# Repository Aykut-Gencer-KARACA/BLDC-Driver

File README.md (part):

<div align="center">

<br/>

<br/><br/>

**Sıfırdan tasarlanmış bir fırçasız DC (BLDC) motor sürücüsü.**<br/>
Hall sensörü olmadan, boştaki fazın back-EMF sıfır geçişini okuyarak rotor konumunu tahmin eder.

<br/>

<sub>PCB'nin Blender'da hazırlanmış 3D render'ı · tam çözünürlüklü video için görsele tıklayın</sub>

</div>

<!--
  ────────────────────────────────────────────────────────────────────────────
  OYNATILABİLİR VİDEO (isteğe bağlı)
  GitHub, repodaki .mp4 dosyalarını README içinde oynatıcı olarak GÖSTERMEZ.
  Oynatıcı istiyorsanız:
    1) GitHub'da README.md'yi web editöründe açın (kalem simgesi).
    2) assets/pcb-render.mp4 dosyasını editöre sürükleyip bırakın.
    3) Oluşan https://github.com/user-attachments/assets/... satırını
       aşağıdaki "VIDEO_LINKI_BURAYA" satırının yerine koyun (tek başına, kendi satırında).
    4) Bu yorum bloğunu silebilirsiniz.
  ────────────────────────────────────────────────────────────────────────────
-->

<!-- VIDEO_LINKI_BURAYA -->

## İçindekiler

- [Genel bakış](#-genel-bakış)
- [Öne çıkanlar](#-öne-çıkanlar)
- [Sistem mimarisi](#-sistem-mimarisi)
- [Six-step komütasyon](#-six-step-komütasyon)
- [Donanım](#-donanım)
- [Tasarım hesapları](#-tasarım-hesapları)
- [Pin haritası](#-pin-haritası)
- [PCB](#-pcb)
- [Malzeme listesi](#-malzeme-listesi)
- [Depo yapısı](#-depo-yapısı)

## ◆ Genel bakış

Bu proje, bir **A2212 1000 KV** fırçasız motoru **3S LiPo** batarya ile sürmek için tasarlanmış bir ESC'dir (Electronic Speed Controller). Kart; güç girişi koruması, iki ayrı regülatör, 3 fazlı MOSFET köprüsü, faz başına bağımsız akım ölçümü, back-EMF algılama ve bir **STM32F405** mikrodenetleyiciyi tek bir PCB üzerinde topluyor.

Tasarımdaki her değer bir hesaba dayanıyor: MOSFET seçiminden bootstrap kondansatörüne, dead-time'dan ferrit bead bastırma oranına kadar kararların gerekçesi [Tasarım hesapları](#-tasarım-hesapları) bölümünde.

| Özellik | Değer |
|---|---|
| **Kontrol yöntemi** | Sensörsüz six-step (trapezoidal), back-EMF sıfır geçişi |
| **Giriş gerilimi** | 3S LiPo · 11.1 V nominal · 12.6 V maksimum |
| **Faz akımı** | 10 A sürekli · 12 A tepe (tasarım hedefi) |
| **Anahtarlama** | 30 kHz, center-aligned PWM |
| **Dead-time** | 2 katman: TIM1 DTG ≈ 1 µs + DRV8300 sabit ≈ 215 ns (tipik) |
| **Akım ölçümü** | 3 × low-side şönt (10 mΩ) + 3 × INA180A1 (20 V/V), eşzamanlı örnekleme |
| **Hız ayarı** | Panel montaj 10 kΩ potansiyometre |
| **Programlama** | SWD (ST-Link V2) |

## ◆ Öne çıkanlar

<table>
<tr>
<td width="50%" valign="top">

**Katmanlı giriş koruması**<br/>
TVS diyot (SMBJ13A, 14.4 V'ta iletime başlar), 20 A SMD sigorta ve P-kanal ters polarite MOSFET (SP40P04AGHNK). Hot-plug ve anahtarlama kaynaklı gerilim darbelerine karşı koruma.

</td>
<td width="50%" valign="top">

**Faz başına eşzamanlı akım ölçümü**<br/>
Üç şönt ve üç back-EMF kanalı üç ayrı ADC'ye dağıtıldı (ADC1/2/3). TIM1 CH4 tetiklediği anda üç ADC *injected simultaneous* modda aynı sıradaki kanalları aynı anda örnekliyor; fazlar arası zaman kayması yok, DMA gerekmiyor.

</td>
</tr>
<tr>
<td valign="top">

**Isıl hesabı yapılmış MOSFET seçimi**<br/>
DON100N04 (40 V, < 3.5 mΩ, **Q<sub>g</sub> ≈ 40 nC** @ 10 V). 10.5 A'de MOSFET başına ≈ 0.39 W (25 °C); sıcakken (4.46 mΩ) ≈ 0.49 W ve 40 °C ortamda T<sub>J</sub> ≈ 65 °C. Bu kartta tek MOSFET'in ısıl sınırı ≈ 22 A.

</td>
<td valign="top">

**Temiz analog besleme**<br/>
VDDA hattı ferrit bead + 100 nF + 1 µF ile buck ripple'ından ayrıldı. 500 kHz'de tahmini **30–60 kat bastırma** (geçen kısım ≈ %1.6–3). ADC referansı ve CSA beslemesi aynı hattan: ölçüm oransal (ratiometric).

</td>
</tr>
<tr>
<td valign="top">

**Hesaplanmış bootstrap**<br/>
C<sub>BOOT,min</sub> ≈ 47 nF (TI'ın 1 V dalgalanma kuralı), seçilen 100 nF ile **~2× pay** ve ≈ 0.47 V dalgalanma. Üst kol kesintisiz açık kalamayacağı için %100 duty kullanılmıyor.

</td>
<td valign="top">

**Sanal nötr ile back-EMF algılama**<br/>
Faz başına 20 kΩ / 4.99 kΩ bölücü 12.6 V'u ≈ 2.52 V'a indiriyor; 3 × 20 kΩ + 1.65 kΩ'luk sanal nötr aynı ölçekte (sapma ≈ %0.7). Boştaki fazın nötrü kestiği an sıfır geçişi.

</td>
</tr>
</table>

## ◆ Sistem mimarisi

Güç yolu soldan sağa akıyor: batarya, sırasıyla sigorta (F1) ve ters polarite MOSFET'inden (Q7) geçip `V_BUS` barasına ulaşıyor; TVS diyodu (D1) Q7'nin hemen arkasında, bara ile GND arasındadır. Bu baradan üç kol ayrılıyor:

- **TPS54202 buck** → 3.3 V (MCU, CSA'lar, potansiyometre) · 500 kHz senkron
- **BA00BC0WFP LDO** → 8 V GVDD (DRV8300 gate sürme beslemesi) · ≈ 5 mA tipik, en fazla ≈ 11 mA yük
- **3 faz köprü** → motor fazları A / B / C

STM32, TIM1'in 6 tamamlayıcı PWM çıkışıyla DRV8300'ü sürüyor; DRV8300 de bootstrap üzerinden üst kol N-kanal MOSFET'lerin gate'lerini bara geriliminin üstüne taşıyor.

## ◆ Six-step komütasyon

Her elektriksel periyot altı adıma bölünüyor. Her adımda **iki faz aktif** (biri üst koldan PWM'leniyor, diğeri alt koldan sürekli iletimde), **üçüncü faz boşta** kalıyor. Boştaki fazın back-EMF'i sanal nötr seviyesini kestiği anda (sıfır geçişi) rotorun konumu biliniyor ve bir sonraki adıma geçiş zamanlanıyor.

| Adım | 1 | 2 | 3 | 4 | 5 | 6 |
|:--|:-:|:-:|:-:|:-:|:-:|:-:|
| **Üst kol (PWM)** | A | A | B | B | C | C |
| **Alt kol (açık)** | B | C | C | A | A | B |
| **Boşta (BEMF ölçümü)** | C | B | A | C | B | A |

> [!NOTE]
> Motor dururken back-EMF olmadığı için sensörsüz kontrolde **açık döngü başlatma** (open-loop ramp) gerekiyor. Motor yeterli hıza ulaşıp BEMF okunabilir hale geldiğinde kapalı döngüye geçiliyor.

## ◆ Donanım

<details open>
<summary><b>Güç katı</b></summary>
<br/>

| Blok | Parça | Not |
|---|---|---|
| Yarım köprü MOSFET'leri | 6 × **DON100N04** (DFN-8) | 40 V · < 3.5 mΩ · Q<sub>g</sub> ≈ 40 nC · gövde diyodu yeterli, harici Schottky yok |
| Gate dirençleri | 6 × 15 Ω | TI referans tasarımı ve bağımsız hesapla doğrulandı |
| Gate pull-down | 6 × 10 kΩ | Self turn-on koruması |
| Faz kondansatörleri | Faz başına 100 µF + 1 µF + 100 nF | Bulk + decoupling |

</details>

<details>
<summary><b>Gate sürücü — DRV8300</b></summary>
<br/>

- DT pini boşta (ya da GND'de): dahili dead-time ≈ 215 ns (tipik, datasheet)
- Bootstrap: 100 nF, entegre bootstrap diyodu
- GVDD: 8 V LDO çıkışı
- nFAULT çıkışı yok → donanımsal aşırı akım kesmesi (BKIN) yok; akım, şönt + INA180 zinciriyle ölçülüyor

</details>

<details>
<summary><b>Akım ölçümü</b></summary>
<br/>

- 3 × **10 mΩ / 3 W** şönt (2512), alt kol altında (low-side)
- 3 × **INA180A1** (20 V/V) — 12 A'de 2.4 V çıkış
- Çıkışta 100 Ω + 22 nF RC filtre (f<sub>c</sub> ≈ 72 kHz)
- 12-bit ADC ile çözünürlük ≈ **4 mA / LSB**

</details>

<details>
<summary><b>Back-EMF algılama</b></summary>
<br/>

- Faz başına bölücü: 20 kΩ / 4.99 kΩ → 12.6 V faz geriliminde **≈ 2.52 V** ADC girişi
- Sanal nötr: 3 × 20 kΩ yıldız + 1.65 kΩ (R<sub>n</sub> = R<sub>alt</sub>/3) → faz bölücüleriyle aynı ölçek
- Tüm dirençler ±%1; ölçek sapması ≈ %0.7

</details>

<details>
<summary><b>Mikrodenetleyici — STM32F405RGT6</b></summary>
<br/>

- Cortex-M4F · 168 MHz · 1 MB Flash · 192 KB RAM · FPU
- Sıcaklık sınıfı: −40…85 °C (RGT6) · datasheet DS8626
- 8 MHz HSE kristal, 2 × 30 pF yük kondansatörü (C<sub>L</sub> = 20 pF)
- VCAP1/2: 2 × 2.2 µF X5R
- 4 × VDD'ye ayrı 100 nF + ortak 4.7 µF (C47), VBAT → 3.3 V + 100 nF
- NRST: 100 nF + tact switch · BOOT0: 10 kΩ ile GND
- SWD: 4 pinlik 2.54 mm header (3.3 V, SWDIO, SWCLK, GND)

</details>

<details>
<summary><b>Göstergeler (LED)</b></summary>
<br/>

| LED | Görev | Sürüş | Akım |
|---|---|---|---|
| LED1 | Güç göstergesi | 3.3 V → R38 (200 Ω) → LED1 → GND | ≈ 6.5 mA |
| LED2 | SWD aktivite göstergesi | 3.3 V → R39 (200 Ω) → LED2 → Q8 (MMBT5551, low-side) · baz SWCLK'ten R40 (10 kΩ) ile | ≈ 6.5 mA |

- LED2, debugger bağlıyken SWCLK üzerindeki trafikle yanıp söner; MCU pini harcamaz.
- Q8'in baz akımı ≈ 0.26 mA — SWCLK hattını anlamlı ölçüde yüklemez.

</details>

## ◆ Tasarım hesapları

<details>
<summary><b>Giriş koruması: sigorta, ters polarite MOSFET'i, TVS</b></summary>
<br/>

**Sigorta (F1).** 20 A, gecikmeli (time-lag), 32 V DC. Gecikmeli olması motorun kalkış anındaki kısa süreli yüksek akımda gereksiz atmayı önler; 20 A, 10 A'lik çalışma akımının iki katıdır.

**Ters polarite MOSFET'i (Q7, SP40P04AGHNK).** Kayıp karşılaştırması, R<sub>DS(on)</sub> = 4.7 mΩ (V<sub>GS</sub> = −10 V'ta en fazla; tipik 3.7 mΩ) ile:

$$\text{Q7 ile: } P = I^2 \times R_{DS(on)} = 10^2 \times 0.0047 \approx 0.47\text{ W}$$

$$\text{Schottky diyotla: } P = V_F \times I \approx 0.45\text{ V} \times 10\text{ A} \approx 4.5\text{ W}$$

Fark yaklaşık 10 kattır (tipik dirençle ≈ 12 kat). Q7'nin gate–source arasına normalde en fazla 12.6 V gelir; SP40P04AGHNK'nin V<sub>GS</sub> sınırı ±20 V, V<sub>DS</sub> sınırı −40 V'tur.

**TVS (D1, SMBJ13A).** Çalışma gerilimi (V<sub>RWM</sub>) 13 V'tur: 3S'in 12.6 V'luk dolu gerilimine kadar neredeyse hiç akım çekmez (en fazla 5 µA). 14.4–16.5 V arasında iletime başlar (V<sub>BR</sub>) ve en büyük darbe akımında (I<sub>PP</sub> = 27.9 A) gerilimi 21.5 V'ta kenetler (V<sub>C</sub>).

Bu değerler kartın en hassas parçalarına göre seçildi. Bataryadan doğrudan beslenen BA00BC0WFP'nin girişi en fazla 18 V, TPS54202'nin en fazla 30 V'tur; Q7'nin gate–source gerilimi de bara gerilimine eşit olduğu için sınırı ±20 V'tur. Küçük ve orta büyüklükteki darbelerde D1, gerilimi 15–17 V civarında tutar ve bu parçaların hepsi sınırın altında kalır. Yalnızca TVS'in tam nominal darbe akımına yaklaşan çok büyük bir darbede kenetleme gerilimi 18 V'un ve ±20 V'un üstüne çıkabilir. 40 V'luk köprü MOSFET'leri her durumda korunur. 13 V'luk TVS, normal çalışma gerilimiyle iletim eşiği arasında küçük bir pay bırakır; bu yüzden kart yalnızca 3S için uygundur, 4S batarya bağlanmamalıdır.

**Ters bağlantıda D1.** D1 tek yönlü bir TVS'tir ve şemada Q7'nin arkasında, bara tarafındadır. Ters bağlantıda Q7 kapalı kalır ve gövde diyodu ters kutuplanır; bara, D1 dahil, bataryadan ayrılır. Bu yüzden D1 iletime geçmez, F1 atmaz ve kart zarar görmez.

</details>

<details>
<summary><b>MOSFET seçimi</b></summary>
<br/>

Anahtarlama anında akım bir MOSFET'ten diğerine devredilirken yoldaki parazit endüktans aşım üretir:

$$\Delta V \approx L_{\text{parazit}} \times \frac{di}{dt} \qquad\text{(örnek: } 10\text{ nH} \times 0.5\text{ A/ns} = 5\text{ V)}$$

Bu yüzden pratikte bara geriliminin en az 2 katı alınır:

$$V_{DS} \geq 2 \times V_{\text{bara,max}} = 2 \times 12.6\text{ V} = 25.2\text{ V} \quad\Rightarrow\quad 40\text{ V sınıfı}$$

$$I_D \geq 3 \times I_{\text{çalışma}} = 3 \times 10\text{ A} = 30\text{ A} \quad\Rightarrow\quad \text{DON100N04: 100 A}$$

İletim kaybı, 25 °C'de $R_{DS(on)} \leq 3.5\text{ m}\Omega$ ile:

$$P = I^2 \times R_{DS(on)} = 10.5^2 \times 0.0035 \approx 0.39\text{ W}$$

Asıl karar ısıl hesapla verilir. Datasheet'teki 100 A (T<sub>C</sub> = 25 °C) ve 59 A (T<sub>C</sub> = 125 °C) değerleri, sonsuz soğutucu varsayımıyla (R<sub>θCA</sub> = 0) yapılmış ısı hesabıdır: $P_{max} = 25/1.6 \approx 15.6\text{ W}$, $I_D = \sqrt{15.6/0.00446} \approx 59\text{ A}$. Bu kartta soğutucu yoktur; ısı PCB bakırından havaya atılır. Sıcakken (150 °C) direnç ≈ 4.46 mΩ, R<sub>θJA</sub> = 50 °C/W ve T<sub>A</sub> = 40 °C ile:

$$P = 10.5^2 \times 0.00446 \approx 0.49\text{ W} \quad\Rightarrow\quad T_J = T_A + P \times R_{\theta JA} = 40 + 0.49 \times 50 \approx 65\text{ °C}$$

$$I_{max} = \sqrt{\frac{(150 - 40)/50}{0.00446}} = \sqrt{\frac{2.2\text{ W}}{0.00446\ \Omega}} \approx 22\text{ A}$$

Yani bu kartta tek bir MOSFET'in sürekli taşıyabileceği akım datasheet'teki 100 A değil, yaklaşık 22 A'dir. Datasheet'teki en kötü parça (25 °C'de 3.5 mΩ, tipikten ≈ 1.25 kat dirençli) için P ≈ 0.61 W ve T<sub>J</sub> ≈ 71 °C olur; sonuç değişmez. Six-step'te bir MOSFET bir elektriksel turun yalnızca bir kısmında akım taşıdığı için gerçek ortalama ısı bundan da düşüktür.

</details>

<details>
<summary><b>Bara kondansatörleri</b></summary>
<br/>

Üst MOSFET her açıldığında motor akımı (≈ 10 A) bir anda bu kola akmak ister; batarya kablo ve PCB izlerinin endüktansı yüzünden bu ani talebe yetişemez. Bu yüzden her kolun yanına faz başına 100 µF + 1 µF + 100 nF konur: 100 µF'lık elektrolitik yükün büyük kısmını depolar, 1 µF ve 100 nF'lık seramikler MHz mertebesindeki hızlı akım değişimlerini karşılar. Kondansatörlerin MOSFET'lerin dibinde olması hızlı akım döngüsünü kısaltır, aşımı azaltır. Motor sargısı bu döngünün içinde değildir; endüktansı büyük olduğu için anahtarlama süresince sabit bir akım kaynağı gibi davranır.

</details>

<details>
<summary><b>Gate sürme: neden sürücü, gate direnci, tepe ve ortalama akım</b></summary>
<br/>

STM32 MOSFET'leri doğrudan süremez:

1. **Gerilim yetmez:** pin en fazla 3.3 V verir; MOSFET'in R<sub>DS(on)</sub> değeri 4.5 V ve 10 V için verilmiştir.
2. **Akım yetmez:** 40 nC'luk gate'i bir GPIO'nun 25 mA'iyle doldurmak $t \approx Q_g / I = 40\text{ nC} / 25\text{ mA} \approx 1.6\ \mu\text{s}$ sürer; DRV8300'ün 0.75 A'iyle aynı süre ≈ 53 ns'dir.
3. **Üst MOSFET'in gate'i baranın üstüne çıkmalı:** source 12.6 V'a çıkınca gate ≈ 20 V civarında olmalıdır; bunu sürücü bootstrap devresiyle üretir.

15 Ω seri gate direnci gate'in dolma hızını yumuşatır (di/dt ve aşım düşer) ve sürücünün tepe akımını sınırlar; daha büyük direnç daha yumuşak ama daha yavaş (daha sıcak) anahtarlama demektir. 10 kΩ pull-down gate'i source seviyesinde tutar.

$$I_{\text{tepe}} = \frac{V_{GVDD}}{R_{toplam}} = \frac{8\text{ V}}{15\ \Omega} \approx 0.53\text{ A}$$

Sürücünün ve MOSFET'in iç dirençleri eklendiği için gerçek tepe akım bunun biraz altında kalır; DRV8300'ün 750 mA'lik (tipik) açma ve 1.5 A'lik kapama akımının altındadır.

$$I_{\text{ort}} \approx \frac{I_{\text{tepe}}}{2} = \frac{0.53}{2} \approx 0.27\text{ A} \qquad t_{\text{şarj}} \approx \frac{Q_g}{I_{\text{ort}}} = \frac{32\text{ nC}}{0.27\text{ A}} \approx 120\text{ ns}$$

120 ns, 30 kHz'lik PWM periyodunun (33 µs) binde dördü kadardır. Gate 8 V ile sürüldüğü için taşınan yük ≈ 32 nC'dur; hesaplarda 40 nC kullanmak güvenli taraftır.

</details>

<details>
<summary><b>Bootstrap kondansatörü</b></summary>
<br/>

Üst kol MOSFET'ini iletimde tutmak için gate'in source'un 8 V üstünde olması gerekir; source bara gerilimine (12.6 V) fırladığı için gate sabit 8 V ile sürülemez. Gate, SH ile birlikte yükselip alçalan bir kondansatörden (C<sub>boot</sub>) beslenir:

- **Şarj fazı:** alt MOSFET iletimdeyken SH ≈ 0 V; GVDD, DRV8300 içindeki bootstrap diyodu üzerinden kondansatörü doldurur. Diyot düşümü (en fazla 0.85 V) yüzünden kondansatörde 8 − 0.85 ≈ 7.15 V birikir.
- **Sürüş fazı:** üst MOSFET iletime geçer, SH 12.6 V'a çıkar; kondansatörün üst ucu 12.6 + 7.15 ≈ 19.8 V'ta kalır ve gate bu noktadan beslenir.

Kondansatörün boyutu (TI'ın yöntemiyle, V<sub>GVDD</sub> = 8 V, Q<sub>g</sub> = 40 nC, f<sub>sw</sub> = 30 kHz):

$$\Delta V_{BST} = V_{GVDD} - V_{BOOTD} - V_{BSTUV} = 8 - 0.85 - 4.5 = 2.65\text{ V}$$

$$Q_{tot} = Q_g + \frac{I_{LBS,TRAN}}{f_{sw}} = 40\text{ nC} + \frac{220\ \mu\text{A}}{30\text{ kHz}} \approx 47\text{ nC}$$

TI, kondansatör üzerindeki çevrim başına dalgalanmanın 1 V'u geçmemesini öneriyor:

$$C_{BOOT,min} = \frac{Q_{tot}}{1\text{ V}} \approx 47\text{ nF} \quad\Rightarrow\quad 100\text{ nF seçildi (yaklaşık 2 kat pay)}$$

100 nF ile dalgalanma $47\text{ nC} / 100\text{ nF} \approx 0.47\text{ V}$, yani 2.65 V'luk sınırın çok altında. GVDD tarafında kural $C_{GVDD} \geq 10 \times C_{BOOT} = 1\ \mu\text{F}$; datasheet GVDD pininde ayrıca en az 10 µF istiyor (C43 = 10 µF, C40 = 1 µF, C42 = 100 nF).

</details>

<details>
<summary><b>GVDD akım bütçesi ve LDO</b></summary>
<br/>

8 V'un gerekçesi: MOSFET tam açılmalı (8 V, datasheet'in R<sub>DS(on)</sub> verdiği 10 V'a yakındır), sürücünün GVDD kilidinden (4.35 V) uzak durulmalı ve batarya boşalırken gate sürüşü sabit kalmalı. Akım çok küçük (≈ 11 mA) olduğu için LDO'nun kaybı önemsizdir.

Six-step'te her an yalnızca PWM uygulanan koldaki iki MOSFET anahtarlanır:

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
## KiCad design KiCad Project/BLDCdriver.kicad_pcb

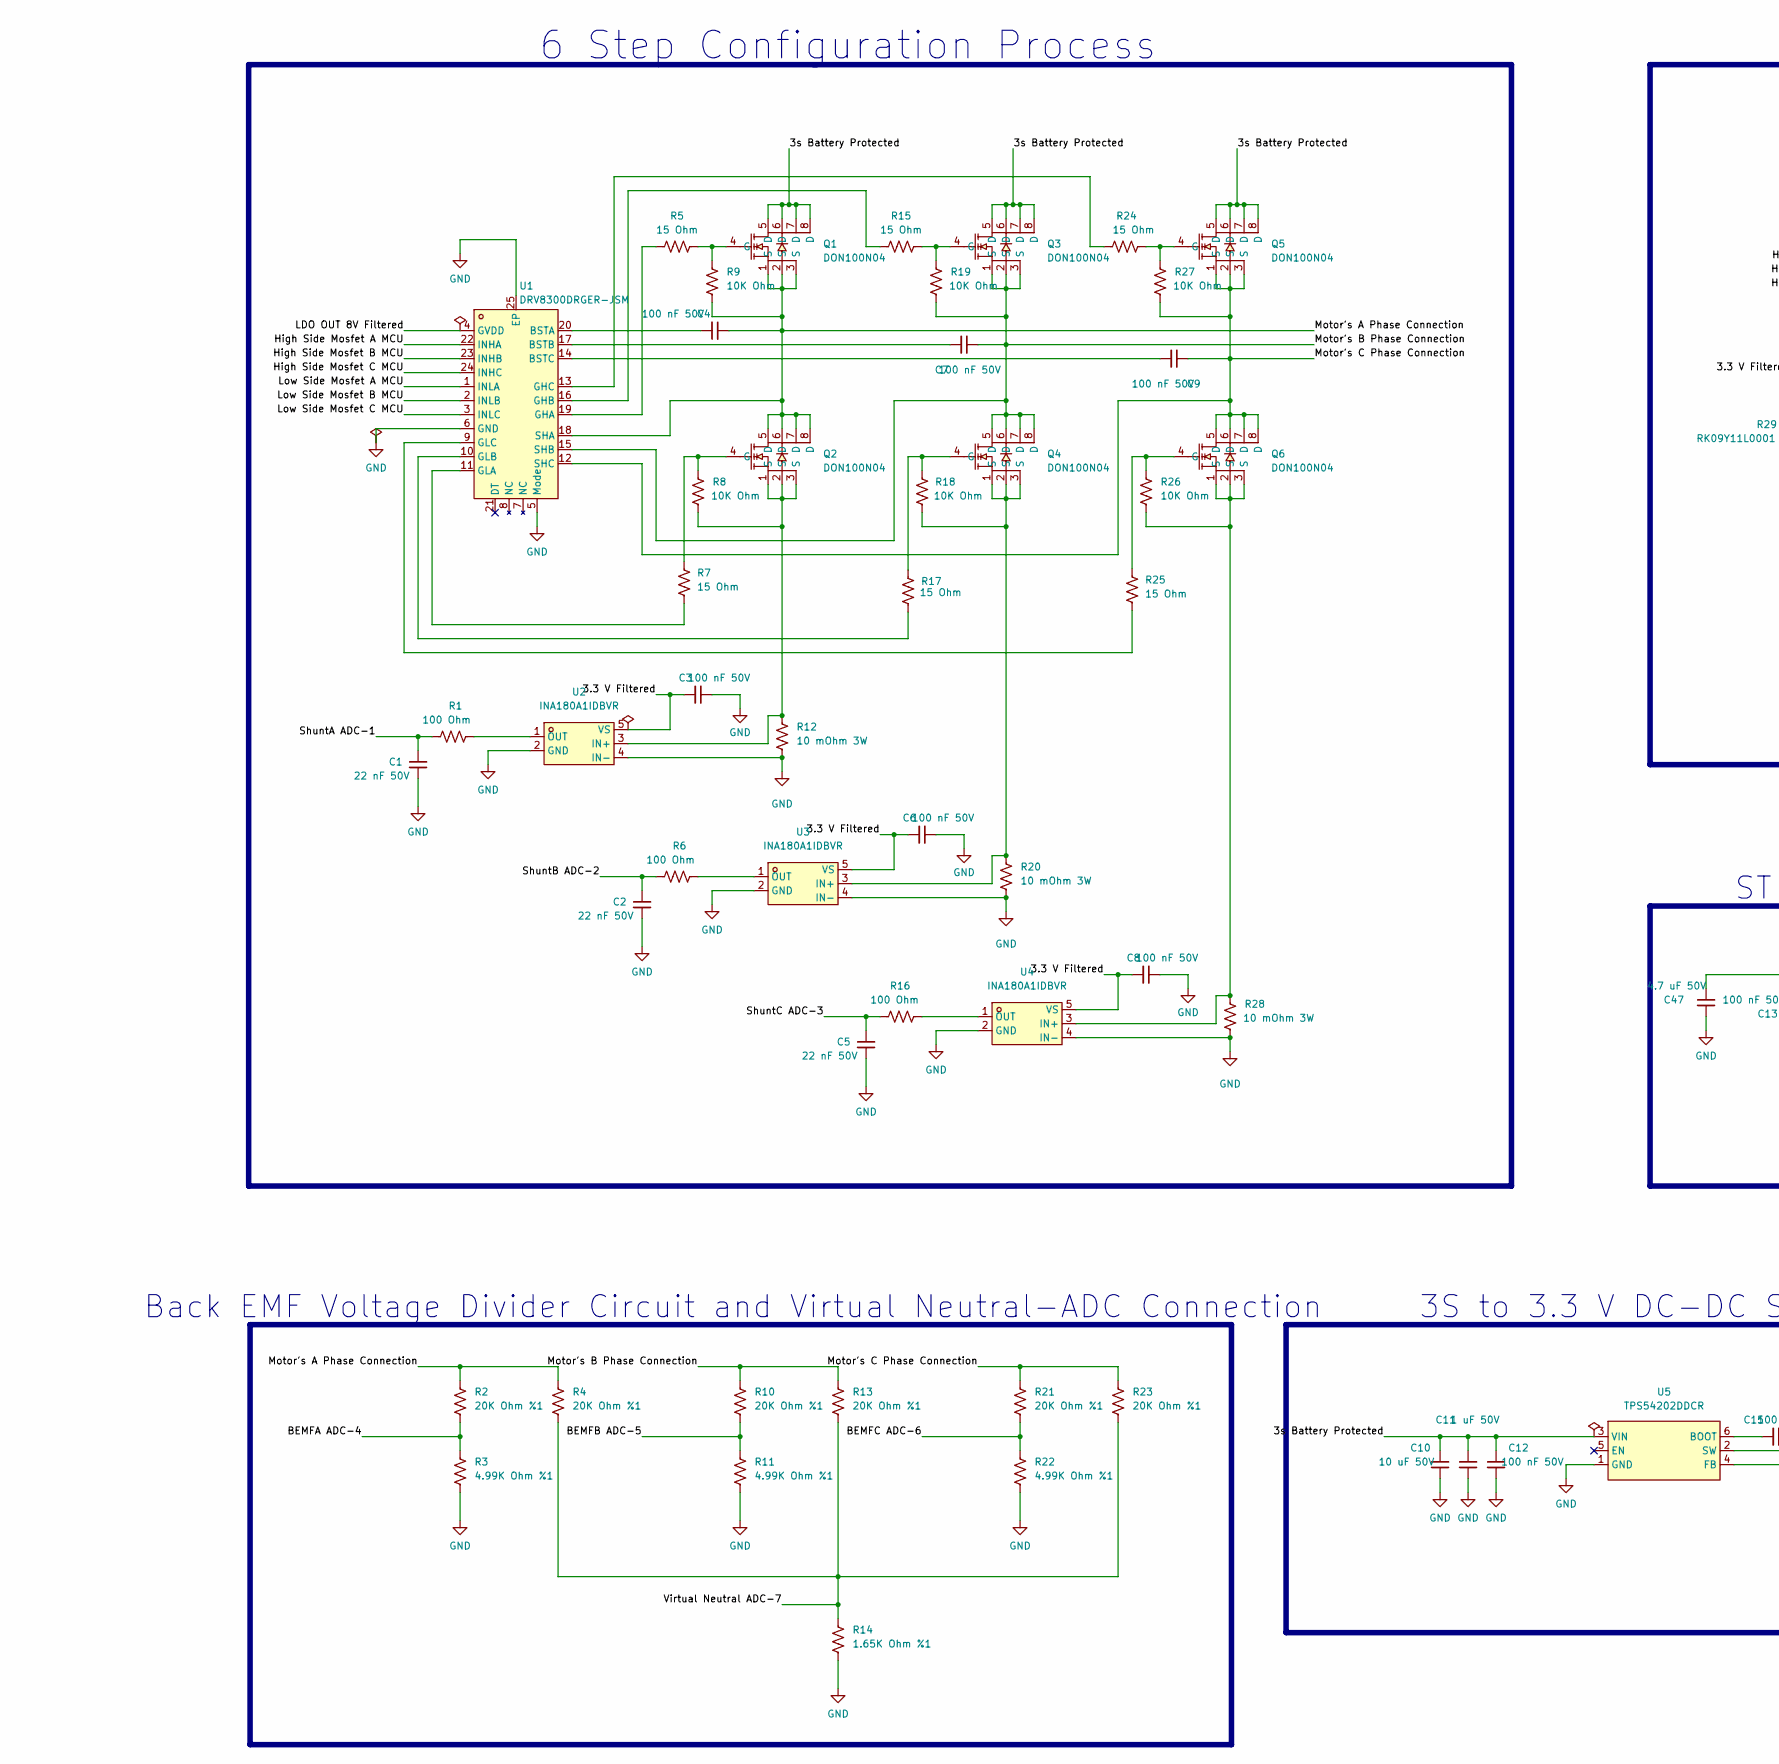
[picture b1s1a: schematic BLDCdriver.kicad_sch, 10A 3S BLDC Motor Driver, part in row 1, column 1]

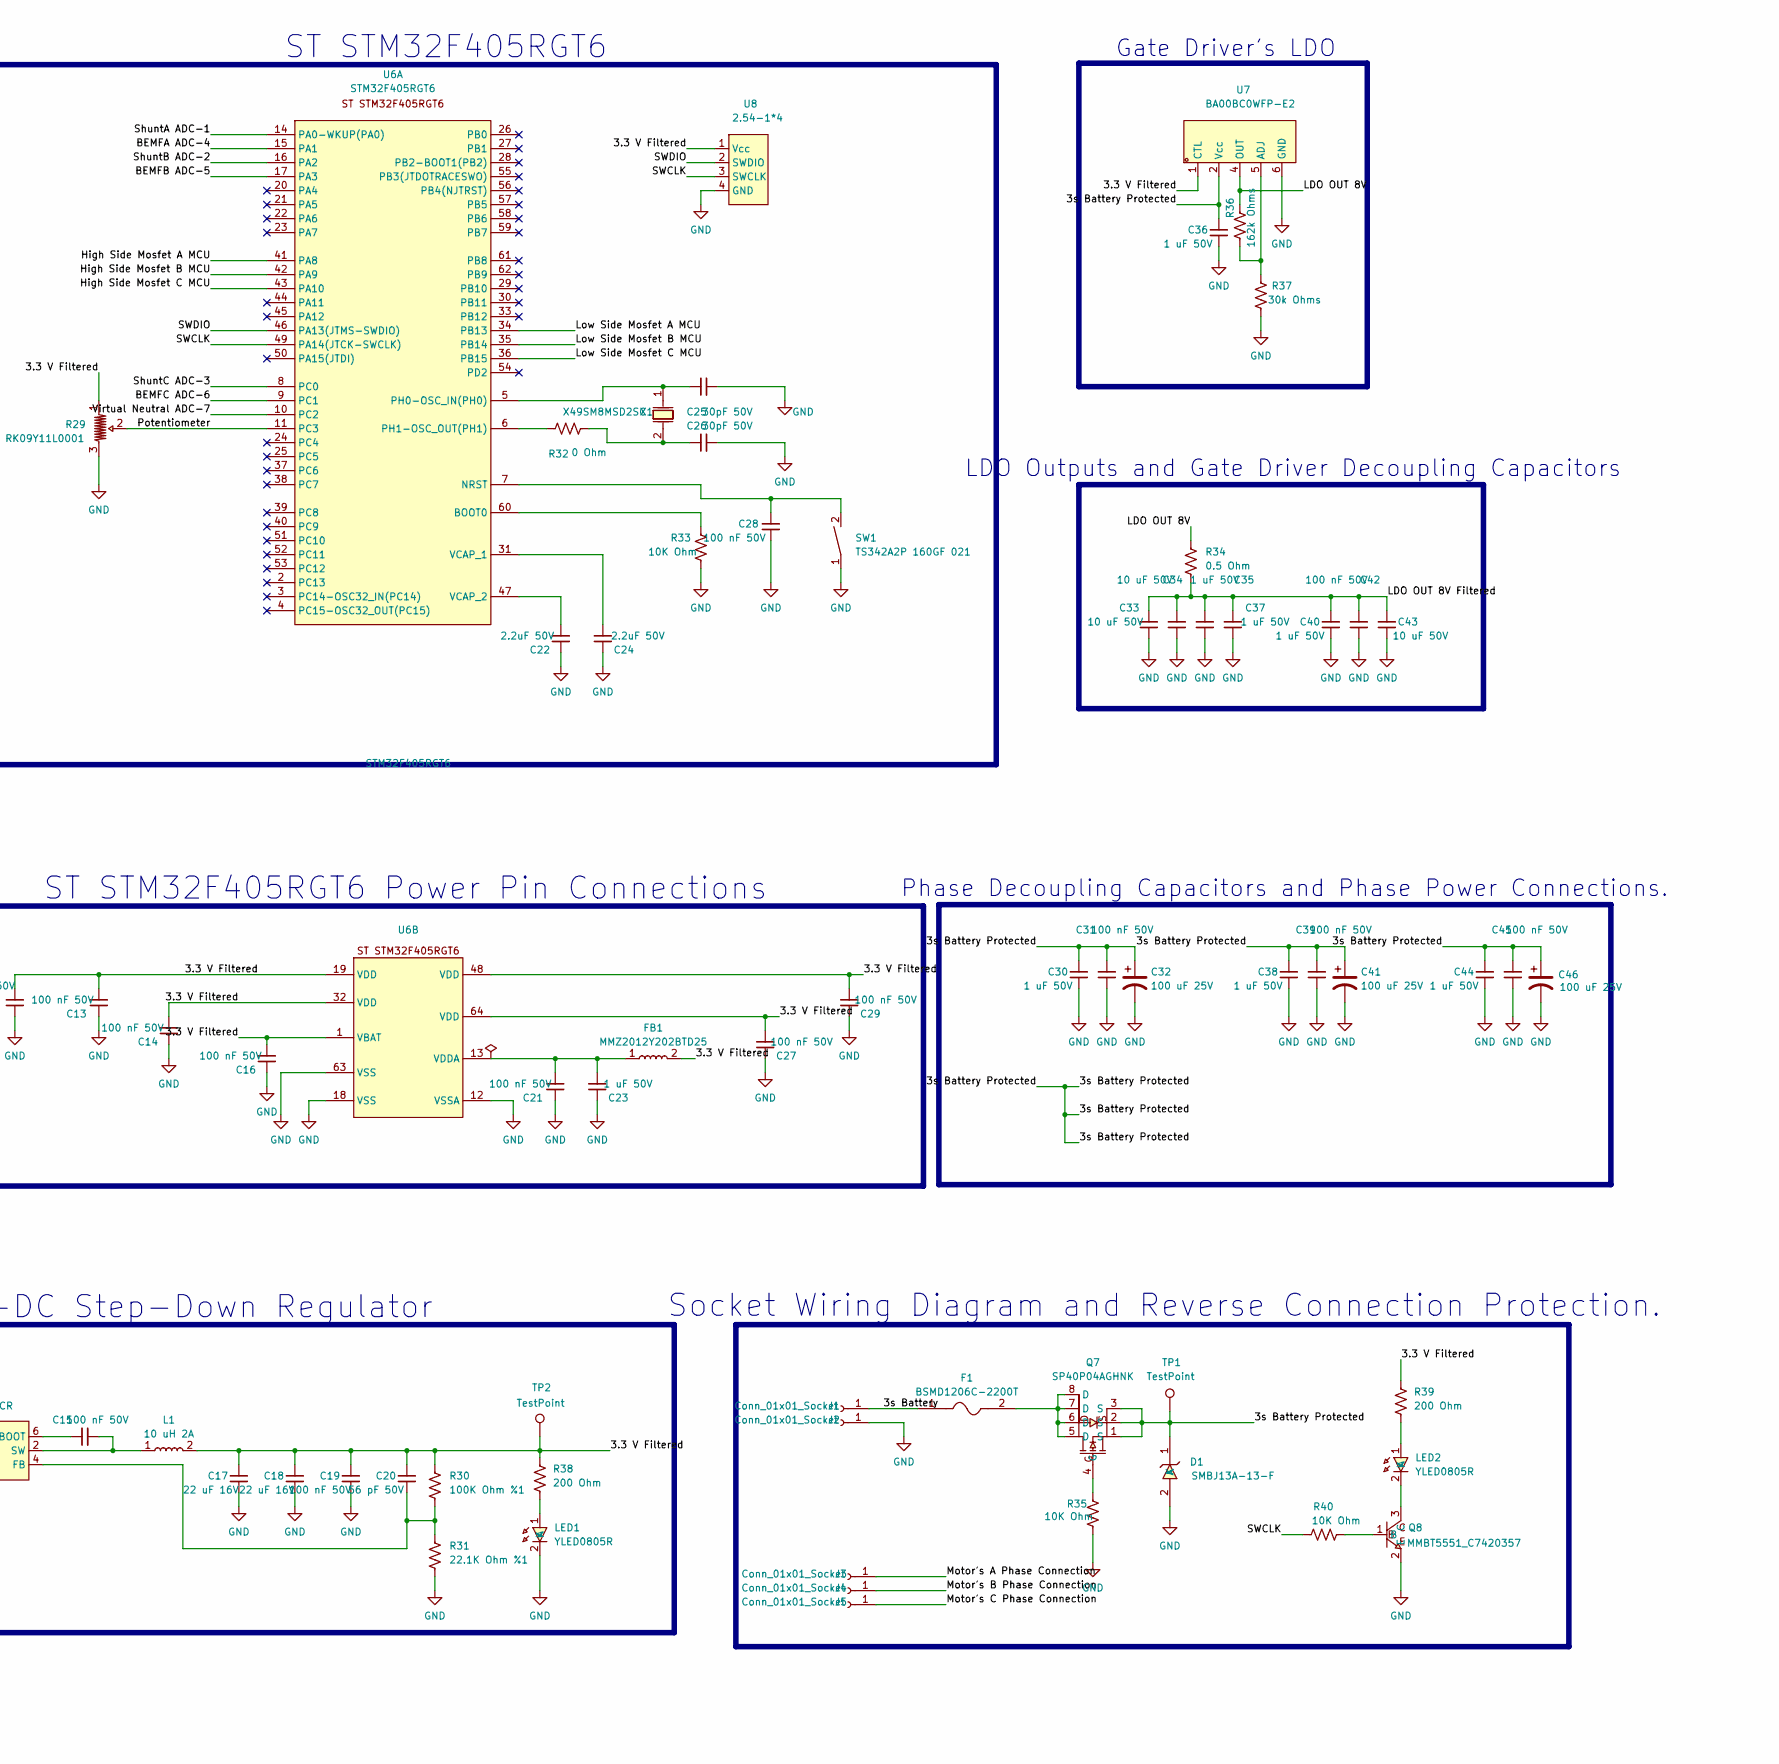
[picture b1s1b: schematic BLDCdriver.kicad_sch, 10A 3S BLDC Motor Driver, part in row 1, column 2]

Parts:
C1, C2, C5: 22 nF 50V; C_0603_1608Metric; LCSC Part C21122
C3, C4, C6, C7, C8, C9, C12, C13, C14, C15, C16, C19, C21, C27, C28, C29, C31, C39, C42, C45: 100 nF 50V; C_0603_1608Metric; LCSC Part C14663
C10, C33, C34, C43: 10 uF 50V; C_1206_3216Metric; LCSC Part C13585
C11, C23, C30, C35, C36, C37, C38, C40, C44: 1 uF 50V; C_0603_1608Metric; LCSC Part C5199872
C17, C18: 22 uF 16V; C_1206_3216Metric; LCSC Part C5448976
C20: 56 pF 50V; C_0603_1608Metric; LCSC Part C107053
C22, C24: 2.2uF 50V; C_0603_1608Metric; LCSC Part C913904
C25, C26: 30pF 50V; C_0603_1608Metric; LCSC Part C113797
C32, C41, C46: 100 uF 25V; CP_Elec_6.3x7.7; LCSC Part C46528102
C47: 4.7 uF 50V; C_0805_2012Metric; LCSC Part C7107661
D1: SMBJ13A-13-F; SMB_L4.6-W3.6-LS5.3-RD; LCSC Part C135042
F1: BSMD1206C-2200T; F1206; LCSC Part C41398512
FB1: MMZ2012Y202BTD25; L0805; LCSC Part C360718
J1, J2, J3, J4, J5: Conn_01x01_Socket; SolderWirePad_1x01_SMD_3x6mm
L1: 10 uH 2A; IND-SMD_L5.4-W5.1; LCSC Part C325986
LED1, LED2: YLED0805R; LED0805-R-RD_RED; LCSC Part C19171391
Q1, Q2, Q3, Q4, Q5, Q6: DON100N04; DFN-8_L5.8-W4.9-P1.27-LS6.1-BL-2; LCSC Part C41430596
Q7: SP40P04AGHNK; DFN-8_L5.8-W4.9-P1.27-LS6.1-BL-2; LCSC Part C45351227
Q8: MMBT5551_C7420357; SOT-23-3_L2.9-W1.3-P1.90-LS2.4-BR; LCSC Part C7420357
R1, R6, R16: 100 Ohm; R_0805_2012Metric; LCSC Part C17408
R2, R4, R10, R13, R21, R23: 20K Ohm %1; R_0805_2012Metric; LCSC Part C2907240
R3, R11, R22: 4.99K Ohm %1; R_0805_2012Metric; LCSC Part C2933454
R5, R7, R15, R17, R24, R25: 15 Ohm; R_0805_2012Metric; LCSC Part C17480
R8, R9, R18, R19, R26, R27, R33, R35, R40: 10K Ohm; R_0805_2012Metric; LCSC Part C2907219
R12, R20, R28: 10 mOhm 3W; R_2512_6332Metric; LCSC Part C5375464
R14: 1.65K Ohm %1; R_0805_2012Metric; LCSC Part C2933334
R29: RK09Y11L0001; RES-ADJ-TH_RK09Y11L0001; LCSC Part C470717
R30: 100K Ohm %1; R_0805_2012Metric; LCSC Part C149504
R31: 22.1K Ohm %1; R_0805_2012Metric; LCSC Part C17552
R32: 0 Ohm; R_0805_2012Metric; LCSC Part C17477
R34: 0.5 Ohm; R_0805_2012Metric; LCSC Part C2934267
R36: 162k Ohms; R_0805_2012Metric; LCSC Part C17486
R37: 30k Ohms; R_0805_2012Metric; LCSC Part C2907255
R38, R39: 200 Ohm; R_0805_2012Metric; LCSC Part C2907239
SW1: TS342A2P 160GF 021; KEY-SMD_L3.9-W3.0-LS5.0; LCSC Part C5373431
TP1, TP2: TestPoint; TestPoint_Pad_D2.0mm
U1: DRV8300DRGER-JSM; QFN-24_L4.0-W4.0-P0.50-BL-EP2.7; LCSC Part C3655801
U2, U3, U4: INA180A1IDBVR; SOT-23-5_L3.0-W1.7-P0.95-LS2.8-BR; LCSC Part C122228
U5: TPS54202DDCR; SOT-23-6_L2.9-W1.6-P0.95-LS2.8-BL; LCSC Part C191884
U6: STM32F405RGT6; LQFP-64_L10.0-W10.0-P0.50-LS12.0-BL; LCSC Part C15742
U7: BA00BC0WFP-E2; TO-252-5_L6.5-W5.5-P1.30-LS10.0-BR; LCSC Part C308578
U8: 2.54-1*4; HDR-TH_4P-P2.54-V-M-1; LCSC Part C5116483
X1: X49SM8MSD2SC; CRYSTAL-SMD_L11.5-W4.8-LS12.7; LCSC Part C12674

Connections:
/3.3 V Filtered: C3.1, C6.1, C8.1, C13.2, C14.2, C16.2, C17.2, C18.2, C19.2, C20.2, C27.2, C29.2, C47.2, FB1.2, L1.2, R29.1, R30.1, R38.1, R39.1, TP2.1 (1_1), U2.5 (VS), U3.5 (VS), U4.5 (VS), U6.1 (VBAT), U6.19 (VDD), U6.32 (VDD), U6.48 (VDD), U6.64 (VDD), U7.1 (CTL), U8.1 (Vcc)
/3s Battery: F1.1, J1.1 (Pin_1_1)
/3s Battery Protected: C10.2, C11.2, C12.1, C30.2, C31.2, C32.1, C36.2, C38.2, C39.2, C41.1, C44.2, C45.2, C46.1, D1.1 (K), Q1.5 (D), Q1.6 (D), Q1.7 (D), Q1.8 (D), Q3.5 (D), Q3.6 (D), Q3.7 (D), Q3.8 (D), Q5.5 (D), Q5.6 (D), Q5.7 (D), Q5.8 (D), Q7.1 (S), Q7.2 (S), Q7.3 (S), TP1.1 (1_1), U5.3 (VIN), U7.2 (Vcc)
/BEMFA ADC-4: R2.2, R3.1, U6.15 (PA1)
/BEMFB ADC-5: R10.2, R11.1, U6.17 (PA3)
/BEMFC ADC-6: R21.2, R22.1, U6.9 (PC1)
/High Side Mosfet A MCU: U1.22 (INHA), U6.41 (PA8)
/High Side Mosfet B MCU: U1.23 (INHB), U6.42 (PA9)
/High Side Mosfet C MCU: U1.24 (INHC), U6.43 (PA10)
/LDO OUT 8V: R34.1, R36.1, U7.4 (OUT)
/LDO OUT 8V Filtered: C33.2, C34.2, C35.2, C37.2, C40.2, C42.2, C43.2, R34.2, U1.4 (GVDD)
/Low Side Mosfet A MCU: U1.1 (INLA), U6.34 (PB13)
/Low Side Mosfet B MCU: U1.2 (INLB), U6.35 (PB14)
/Low Side Mosfet C MCU: U1.3 (INLC), U6.36 (PB15)
/Motor's A Phase Connection: C4.2, J3.1 (Pin_1_1), Q1.1 (S), Q1.2 (S), Q1.3 (S), Q2.5 (D), Q2.6 (D), Q2.7 (D), Q2.8 (D), R2.1, R4.1, R9.2, U1.18 (SHA)
/Motor's B Phase Connection: C7.2, J4.1 (Pin_1_1), Q3.1 (S), Q3.2 (S), Q3.3 (S), Q4.5 (D), Q4.6 (D), Q4.7 (D), Q4.8 (D), R10.1, R13.1, R19.2, U1.15 (SHB)
/Motor's C Phase Connection: C9.2, J5.1 (Pin_1_1), Q5.1 (S), Q5.2 (S), Q5.3 (S), Q6.5 (D), Q6.6 (D), Q6.7 (D), Q6.8 (D), R21.1, R23.1, R27.2, U1.12 (SHC)
/Potentiometer: R29.2, U6.11 (PC3)
/SWCLK: R40.1, U6.49 (PA14(JTCK-SWCLK)), U8.3 (SWCLK)
/SWDIO: U6.46 (PA13(JTMS-SWDIO)), U8.2 (SWDIO)
/ShuntA ADC-1: C1.2, R1.1, U6.14 (PA0-WKUP(PA0))
/ShuntB ADC-2: C2.2, R6.1, U6.16 (PA2)
/ShuntC ADC-3: C5.2, R16.1, U6.8 (PC0)
/Virtual Neutral ADC-7: R4.2, R13.2, R14.1, R23.2, U6.10 (PC2)
GND: C1.1, C2.1, C3.2, C5.1, C6.2, C8.2, C10.1, C11.1, C12.2, C13.1, C14.1, C16.1, C17.1, C18.1, C19.1, C21.1, C22.1, C23.1, C24.1, C25.2, C26.2, C27.1, C28.1, C29.1, C30.1, C31.1, C32.2, C33.1, C34.1, C35.1, C36.1, C37.1, C38.1, C39.1, C40.1, C41.2, C42.1, C43.1, C44.1, C45.1, C46.2, C47.1, D1.2 (A), J2.1 (Pin_1_1), LED1.2 (K), Q8.2 (E), R3.2, R11.2, R12.2, R14.2, R20.2, R22.2, R28.2, R29.3, R31.2, R33.2, R35.2, R37.1, SW1.1, U1.5 (Mode), U1.6 (GND), U1.25 (EP), U2.2 (GND), U2.4 (IN-), U3.2 (GND), U3.4 (IN-), U4.2 (GND), U4.4 (IN-), U5.1 (GND), U6.12 (VSSA), U6.18 (VSS), U6.63 (VSS), U7.6 (GND), U8.4 (GND)
unnamed: C26.1, R32.2, X1.2
unnamed: F1.2, Q7.5 (D), Q7.6 (D), Q7.7 (D), Q7.8 (D)
unnamed: LED1.1 (A), R38.2
unnamed: LED2.1 (A), R39.2
unnamed: LED2.2 (K), Q8.3 (C)
unnamed: Q1.4 (G), R5.2, R9.1
unnamed: Q2.4 (G), R7.1, R8.1
unnamed: Q3.4 (G), R15.2, R19.1
unnamed: Q4.4 (G), R17.1, R18.1
unnamed: Q5.4 (G), R24.2, R27.1
unnamed: Q6.4 (G), R25.1, R26.1
unnamed: Q7.4 (G), R35.1
unnamed: Q8.1 (B), R40.2
unnamed: C4.1, U1.20 (BSTA)
unnamed: C7.1, U1.17 (BSTB)
unnamed: C9.1, U1.14 (BSTC)
unnamed: R5.1, U1.19 (GHA)
unnamed: R15.1, U1.16 (GHB)
unnamed: R24.1, U1.13 (GHC)
unnamed: R7.2, U1.11 (GLA)
unnamed: R17.2, U1.10 (GLB)
unnamed: R25.2, U1.9 (GLC)
unnamed: Q2.1 (S), Q2.2 (S), Q2.3 (S), R8.2, R12.1, U2.3 (IN+)
unnamed: R1.2, U2.1 (OUT)
unnamed: Q4.1 (S), Q4.2 (S), Q4.3 (S), R18.2, R20.1, U3.3 (IN+)
unnamed: R6.2, U3.1 (OUT)
unnamed: Q6.1 (S), Q6.2 (S), Q6.3 (S), R26.2, R28.1, U4.3 (IN+)
unnamed: R16.2, U4.1 (OUT)
unnamed: C15.1, U5.6 (BOOT)
unnamed: C20.1, R30.2, R31.1, U5.4 (FB)
unnamed: C15.2, L1.1, U5.2 (SW)
unnamed: R33.1, U6.60 (BOOT0)
unnamed: C28.2, SW1.2, U6.7 (NRST)
unnamed: C25.1, U6.5 (PH0-OSC_IN(PH0)), X1.1
unnamed: R32.1, U6.6 (PH1-OSC_OUT(PH1))
unnamed: C24.2, U6.31 (VCAP_1)
unnamed: C22.2, U6.47 (VCAP_2)
unnamed: C21.2, C23.2, FB1.1, U6.13 (VDDA)
unnamed: R36.2, R37.2, U7.5 (ADJ)

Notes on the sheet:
Gate Driver's LDO
6 Step Configuration Process
Back EMF Voltage Divider Circuit and Virtual Neutral-ADC Connection
LDO Outputs and Gate Driver Decoupling Capacitors
ST STM32F405RGT6 Power Pin Connections
Phase Decoupling Capacitors and Phase Power Connections.
Socket Wiring Diagram and Reverse Connection Protection.
3S to 3.3 V DC-DC Step-Down Regulator
ST STM32F405RGT6

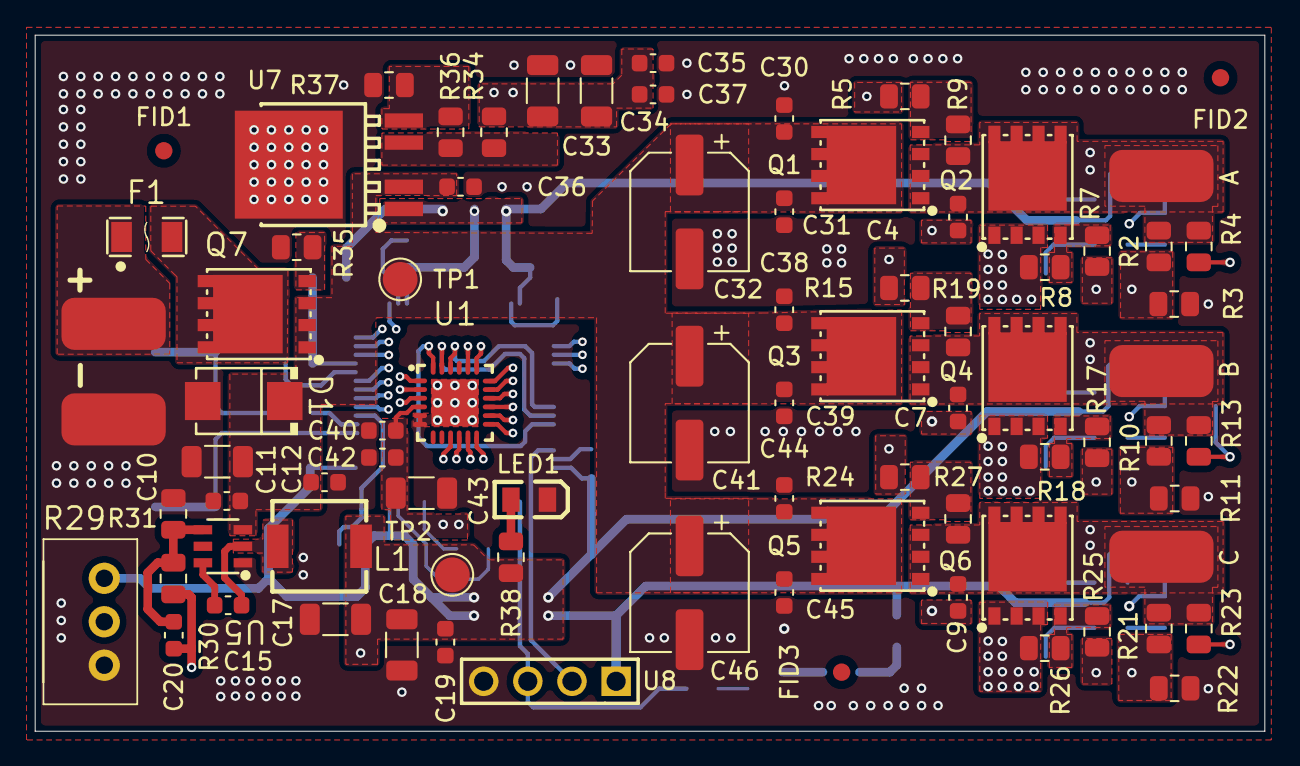
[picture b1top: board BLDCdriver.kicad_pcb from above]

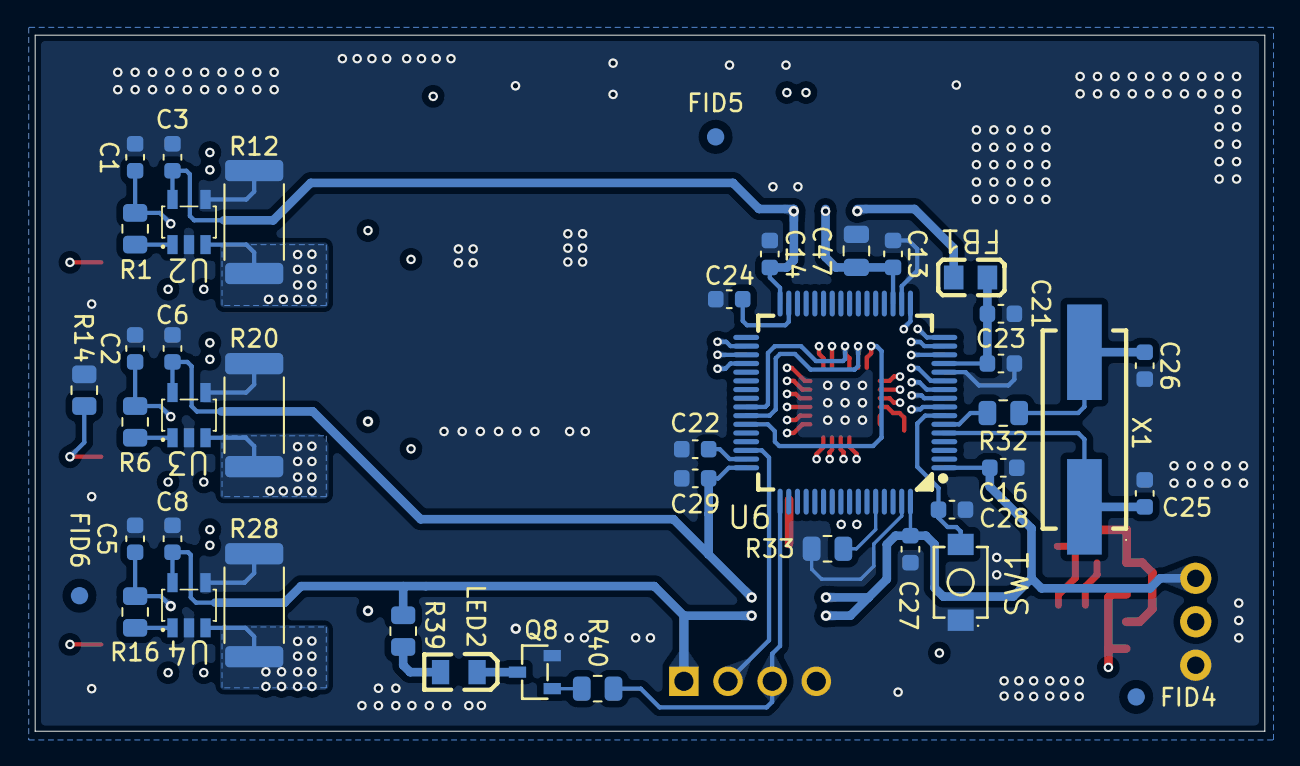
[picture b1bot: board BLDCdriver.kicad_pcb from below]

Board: 6 copper layers, 70.8 x 40.0 mm, 124 parts (42 on the bottom side), 64 nets.

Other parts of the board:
FID1, FID2, FID3, FID4, FID5, FID6: Fiducial_1mm_Mask2mm
